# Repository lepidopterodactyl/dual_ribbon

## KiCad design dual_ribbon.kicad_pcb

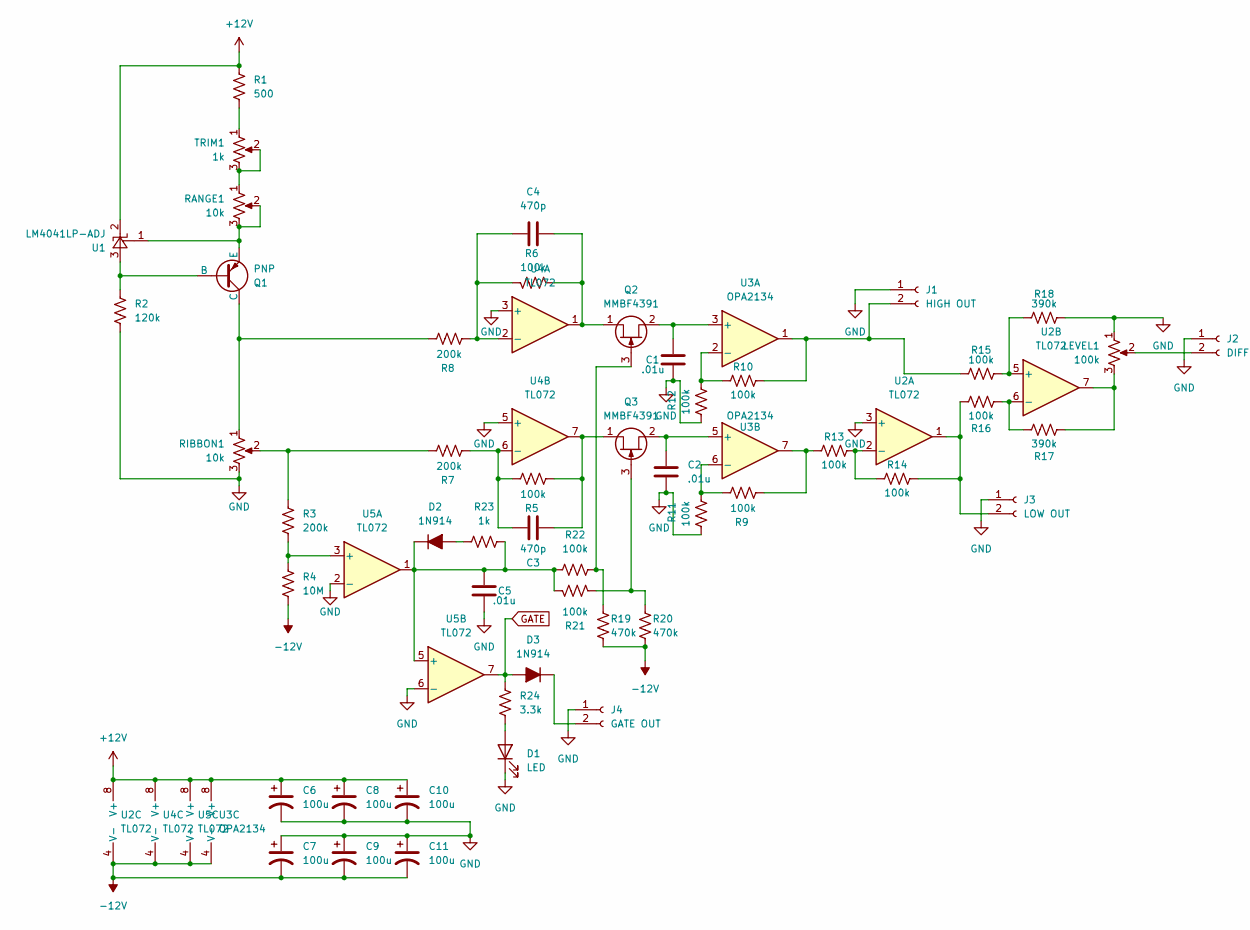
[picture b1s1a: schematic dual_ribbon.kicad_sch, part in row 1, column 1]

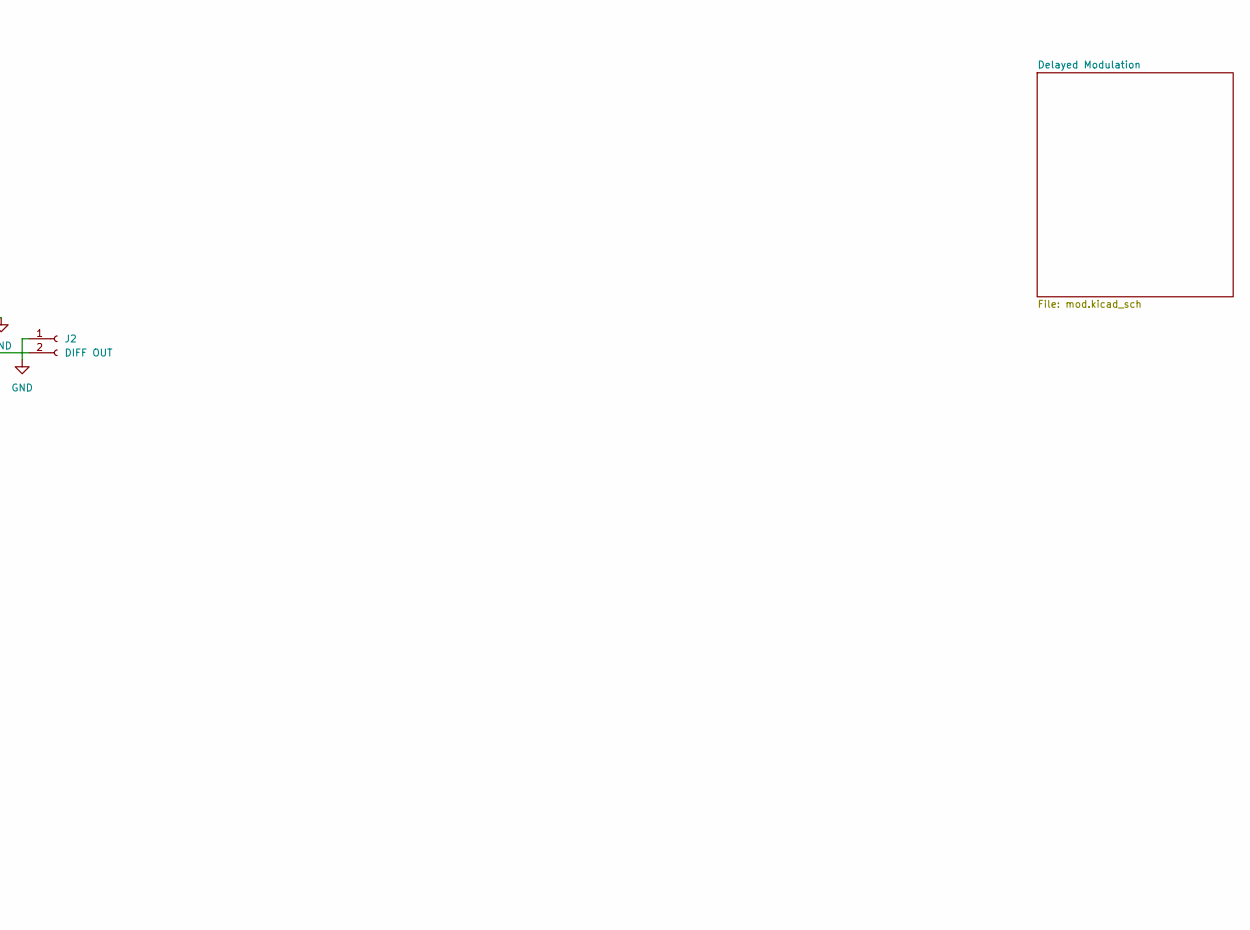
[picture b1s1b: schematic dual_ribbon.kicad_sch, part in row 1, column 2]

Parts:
C1, C2, C5: .01u; C_Rect_L7.2mm_W2.5mm_P5.00mm_FKS2_FKP2_MKS2_MKP2
C3, C4: 470p; C_Rect_L7.2mm_W2.5mm_P5.00mm_FKS2_FKP2_MKS2_MKP2
C6, C7, C8, C9, C10, C11: 100u; CP_Radial_D6.3mm_P2.50mm
D1: LED; LED_D3.0mm
D2, D3: 1N914; D_DO-35_SOD27_P7.62mm_Horizontal
J1: HIGH OUT; SolderWire-0.75sqmm_1x02_P4.8mm_D1.25mm_OD2.3mm
J2: DIFF OUT; SolderWire-0.75sqmm_1x02_P4.8mm_D1.25mm_OD2.3mm
J3: LOW OUT; SolderWire-0.75sqmm_1x02_P4.8mm_D1.25mm_OD2.3mm
J4: GATE OUT; SolderWire-0.75sqmm_1x02_P4.8mm_D1.25mm_OD2.3mm
LEVEL1: 100k; SolderWire-0.75sqmm_1x03_P4.8mm_D1.25mm_OD2.3mm
Q1: PNP; TO-92_Inline
Q2, Q3: MMBF4391; TO-92_Inline
R1: 500; R_Axial_DIN0207_L6.3mm_D2.5mm_P7.62mm_Horizontal
R2: 120k; R_Axial_DIN0207_L6.3mm_D2.5mm_P7.62mm_Horizontal
R3, R7, R8: 200k; R_Axial_DIN0207_L6.3mm_D2.5mm_P7.62mm_Horizontal
R4: 10M; R_Axial_DIN0207_L6.3mm_D2.5mm_P7.62mm_Horizontal
R5, R6, R9, R10, R11, R12, R13, R14, R15, R16, R21, R22: 100k; R_Axial_DIN0207_L6.3mm_D2.5mm_P7.62mm_Horizontal
R17, R18: 390k; R_Axial_DIN0207_L6.3mm_D2.5mm_P7.62mm_Horizontal
R19, R20: 470k; R_Axial_DIN0207_L6.3mm_D2.5mm_P7.62mm_Horizontal
R23: 1k; R_Axial_DIN0207_L6.3mm_D2.5mm_P7.62mm_Horizontal
R24: 3.3k; R_Axial_DIN0207_L6.3mm_D2.5mm_P7.62mm_Horizontal
RANGE1: 10k; SolderWire-0.75sqmm_1x03_P4.8mm_D1.25mm_OD2.3mm
RIBBON1: 10k; SolderWire-0.75sqmm_1x03_P4.8mm_D1.25mm_OD2.3mm
TRIM1: 1k; SolderWire-0.75sqmm_1x03_P4.8mm_D1.25mm_OD2.3mm
U1: LM4041LP-ADJ; TO-92_Inline
U2, U4, U5: TL072; DIP-8_W7.62mm_Socket
U3: OPA2134; DIP-8_W7.62mm_Socket

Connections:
+12V: C6.1, C8.1, C10.1, R1.1, U1.2 (K), U2.8 (V+), U3.8 (V+), U4.8 (V+), U5.8 (V+); also elsewhere on the board
-12V: C7.2, C9.2, C11.2, R4.2, R19.1, R20.1, U2.4 (V-), U3.4 (V-), U4.4 (V-), U5.4 (V-); also elsewhere on the board
GATE: D3.2 (A), R24.1, U5.7; also elsewhere on the board
GND: C1.2, C2.2, C5.2, C6.2, C7.1, C8.2, C9.1, C10.2, C11.1, D1.1 (K), J1.1, J2.1, J3.1, J4.1, LEVEL1.1, R2.2, R11.2, R12.2, R18.2, RIBBON1.3, U2.3 (+), U4.3 (+), U4.5 (+), U5.2 (-), U5.6 (-); also elsewhere on the board
unnamed: D1.2 (A), R24.2
unnamed: C5.1, D2.1 (K), R21.1, R22.1, R23.2, U5.1, U5.5 (+)
unnamed: D2.2 (A), R23.1
unnamed: D3.1 (K), J4.2
unnamed: J1.2, R10.2, R15.1, U3.1
unnamed: J2.2, LEVEL1.2
unnamed: J3.2, R14.2, R16.1, U2.1
unnamed: LEVEL1.3, R17.2, U2.7
unnamed: Q1.2 (B), R2.1, U1.3 (A)
unnamed: Q1.1 (C), R8.1, RIBBON1.1
unnamed: Q1.3 (E), RANGE1.2, RANGE1.3, U1.1 (FB)
unnamed: C4.2, Q2.1 (D), R6.2, U4.1
unnamed: Q2.3 (G), R19.2, R22.2
unnamed: C1.1, Q2.2 (S), U3.3 (+)
unnamed: C3.1, Q3.1 (D), R5.2, U4.7
unnamed: Q3.3 (G), R20.2, R21.2
unnamed: C2.1, Q3.2 (S), U3.5 (+)
unnamed: R1.2, TRIM1.1
unnamed: R3.2, R7.1, RIBBON1.2
unnamed: R9.2, R13.1, U3.7
unnamed: RANGE1.1, TRIM1.2, TRIM1.3
unnamed: R13.2, R14.1, U2.2 (-)
unnamed: R15.2, R18.1, U2.5 (+)
unnamed: R16.2, R17.1, U2.6 (-)
unnamed: R10.1, R12.1, U3.2 (-)
unnamed: R9.1, R11.1, U3.6 (-)
unnamed: C4.1, R6.1, R8.2, U4.2 (-)
unnamed: C3.2, R5.1, R7.2, U4.6 (-)
unnamed: R3.1, R4.1, U5.3 (+)

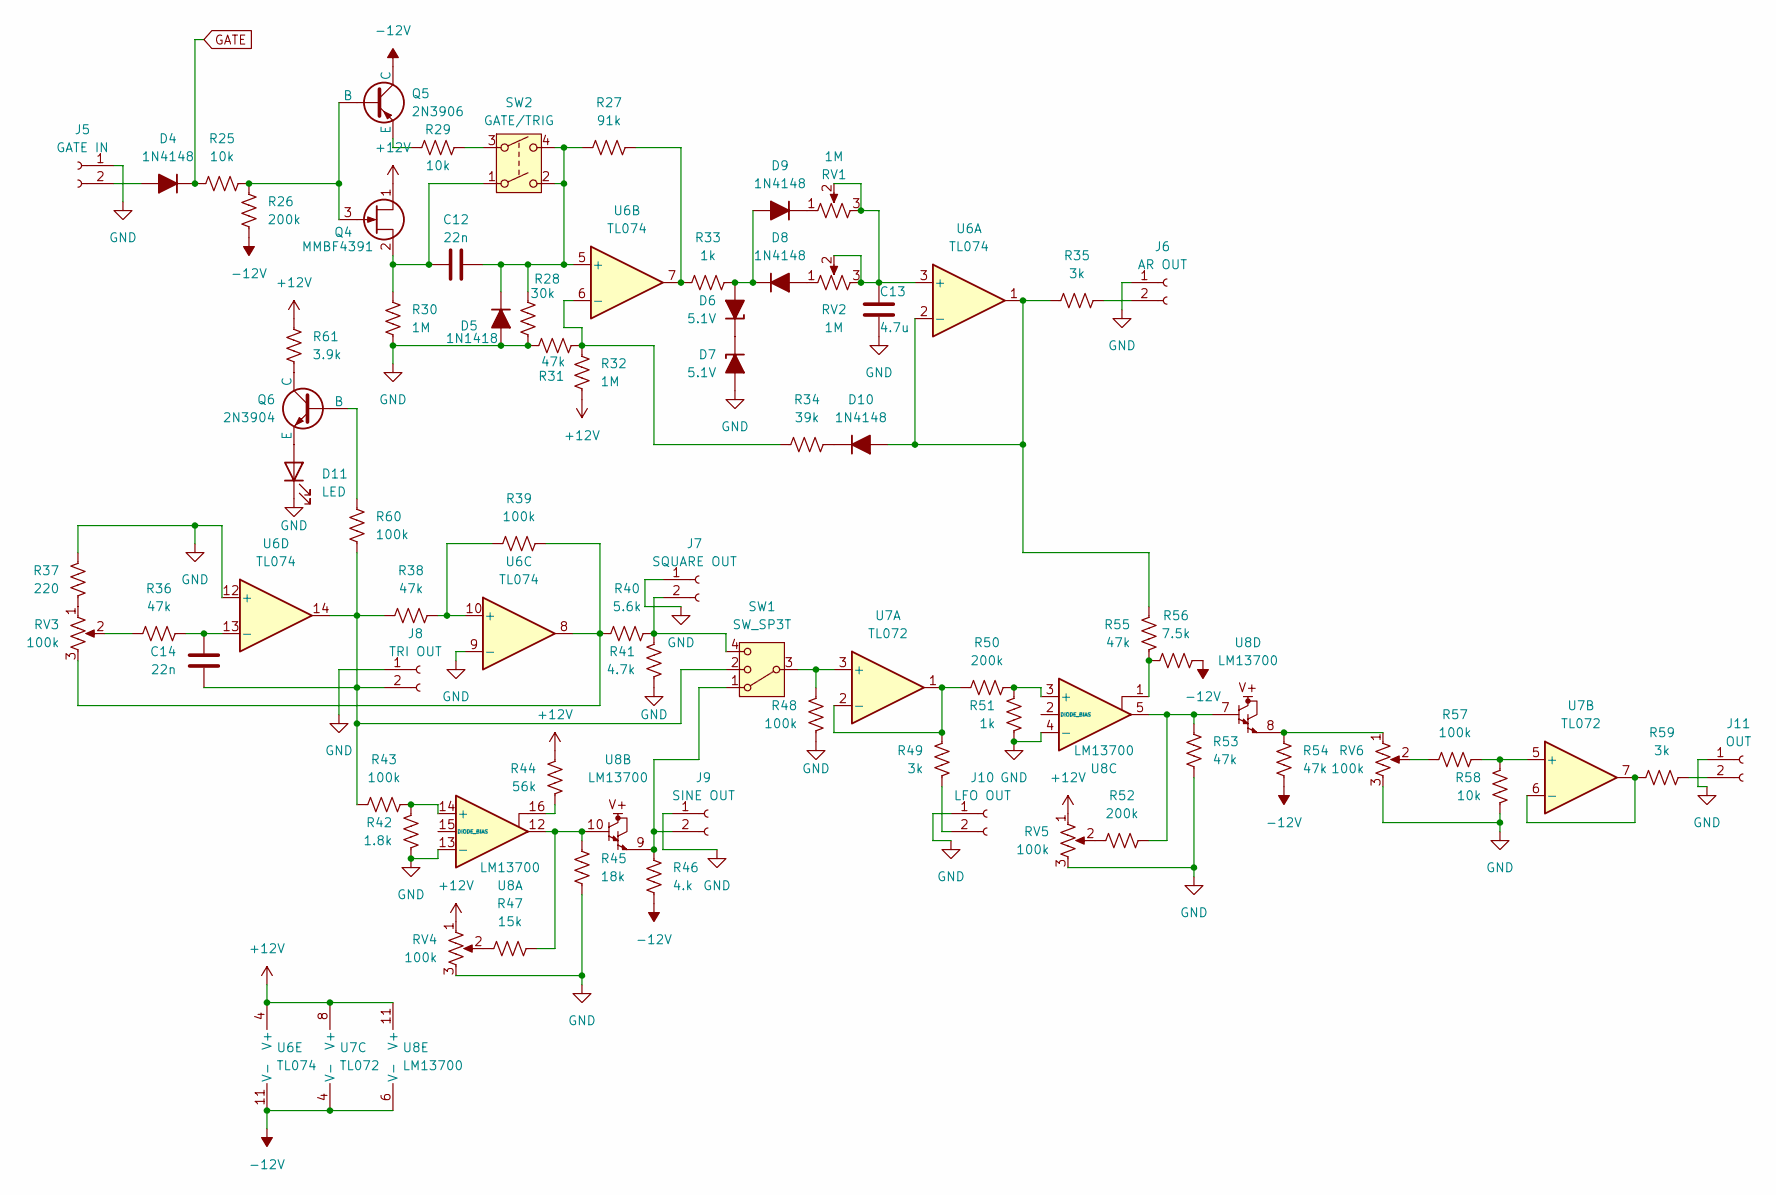
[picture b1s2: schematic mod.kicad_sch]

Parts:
C12, C14: 22n; C_Disc_D3.0mm_W2.0mm_P2.50mm
C13: 4.7u; C_Radial_D6.3mm_H5.0mm_P2.50mm
D4, D8, D9, D10: 1N4148; D_DO-35_SOD27_P7.62mm_Horizontal
D5: 1N1418; D_DO-35_SOD27_P7.62mm_Horizontal
D6, D7: 5.1V; D_DO-35_SOD27_P7.62mm_Horizontal
D11: LED; LED_D3.0mm
J5: GATE IN; SolderWire-0.75sqmm_1x02_P4.8mm_D1.25mm_OD2.3mm
J6: AR OUT; SolderWire-0.75sqmm_1x02_P4.8mm_D1.25mm_OD2.3mm
J7: SQUARE OUT; SolderWire-0.75sqmm_1x02_P4.8mm_D1.25mm_OD2.3mm
J8: TRI OUT; SolderWire-0.75sqmm_1x02_P4.8mm_D1.25mm_OD2.3mm
J9: SINE OUT; SolderWire-0.75sqmm_1x02_P4.8mm_D1.25mm_OD2.3mm
J10: LFO OUT; SolderWire-0.75sqmm_1x02_P4.8mm_D1.25mm_OD2.3mm
J11: OUT; SolderWire-0.75sqmm_1x02_P4.8mm_D1.25mm_OD2.3mm
Q4: MMBF4391; TO-92_Inline
Q5: 2N3906; TO-92_Inline
Q6: 2N3904; TO-92_Inline
R25, R29, R58: 10k; R_Axial_DIN0207_L6.3mm_D2.5mm_P7.62mm_Horizontal
R26, R50, R52: 200k; R_Axial_DIN0207_L6.3mm_D2.5mm_P7.62mm_Horizontal
R27: 91k; R_Axial_DIN0207_L6.3mm_D2.5mm_P7.62mm_Horizontal
R28: 30k; R_Axial_DIN0207_L6.3mm_D2.5mm_P7.62mm_Horizontal
R30, R32: 1M; R_Axial_DIN0207_L6.3mm_D2.5mm_P7.62mm_Horizontal
R31, R36, R38, R53, R54, R55: 47k; R_Axial_DIN0207_L6.3mm_D2.5mm_P7.62mm_Horizontal
R33, R51: 1k; R_Axial_DIN0207_L6.3mm_D2.5mm_P7.62mm_Horizontal
R34: 39k; R_Axial_DIN0207_L6.3mm_D2.5mm_P7.62mm_Horizontal
R35, R49, R59: 3k; R_Axial_DIN0207_L6.3mm_D2.5mm_P7.62mm_Horizontal
R37: 220; R_Axial_DIN0207_L6.3mm_D2.5mm_P7.62mm_Horizontal
R39, R43, R48, R57, R60: 100k; R_Axial_DIN0207_L6.3mm_D2.5mm_P7.62mm_Horizontal
R40: 5.6k; R_Axial_DIN0207_L6.3mm_D2.5mm_P7.62mm_Horizontal
R41: 4.7k; R_Axial_DIN0207_L6.3mm_D2.5mm_P7.62mm_Horizontal
R42: 1.8k; R_Axial_DIN0207_L6.3mm_D2.5mm_P7.62mm_Horizontal
R44: 56k; R_Axial_DIN0207_L6.3mm_D2.5mm_P7.62mm_Horizontal
R45: 18k; R_Axial_DIN0207_L6.3mm_D2.5mm_P7.62mm_Horizontal
R46: 4.k; R_Axial_DIN0207_L6.3mm_D2.5mm_P7.62mm_Horizontal
R47: 15k; R_Axial_DIN0207_L6.3mm_D2.5mm_P7.62mm_Horizontal
R56: 7.5k; R_Axial_DIN0207_L6.3mm_D2.5mm_P7.62mm_Horizontal
R61: 3.9k; R_Axial_DIN0207_L6.3mm_D2.5mm_P7.62mm_Horizontal
RV1, RV2: 1M; SolderWire-0.75sqmm_1x03_P4.8mm_D1.25mm_OD2.3mm
RV3, RV4, RV5, RV6: 100k; SolderWire-0.75sqmm_1x03_P4.8mm_D1.25mm_OD2.3mm
SW1: SW_SP3T; SolderWire-0.75sqmm_1x04_P4.8mm_D1.25mm_OD2.3mm
SW2: GATE/TRIG; SolderWire-0.75sqmm_1x04_P4.8mm_D1.25mm_OD2.3mm
U6: TL074; DIP-14_W7.62mm_Socket
U7: TL072; DIP-8_W7.62mm_Socket
U8: LM13700; DIP-16_W7.62mm_Socket

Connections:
+12V: Q4.1 (D), R32.2, R44.2, R61.1, RV4.1, RV5.1, U6.4 (V+), U7.8 (V+), U8.11 (V+); also elsewhere on the board
-12V: Q5.1 (C), R26.1, R46.1, R54.1, R56.2, U6.11 (V-), U7.4 (V-), U8.6 (V-); also elsewhere on the board
GATE: D4.1 (K), R25.1; also elsewhere on the board
GND: C13.2, D5.2 (A), D7.2 (A), D11.1 (K), J5.1, J6.1, J7.1, J8.1, J9.1, J10.1, J11.1, R28.1, R30.2, R31.1, R37.2, R41.1, R42.1, R45.1, R48.1, R51.1, R53.1, R58.1, RV4.3, RV5.3, RV6.3, U6.9 (-), U6.12 (+), U8.4 (-), U8.13 (-); also elsewhere on the board
unnamed: D4.2 (A), J5.2
unnamed: C12.2, D5.1 (K), R27.1, R28.2, SW2.2, SW2.4, U6.5 (+)
unnamed: D6.2 (A), D8.1 (K), D9.2 (A), R33.2
unnamed: D6.1 (K), D7.1 (K)
unnamed: D8.2 (A), RV2.1
unnamed: D9.1 (K), RV1.1
unnamed: D10.2 (A), R35.1, R55.2, U6.1, U6.2 (-)
unnamed: D10.1 (K), R34.2
unnamed: D11.2 (A), Q6.3 (E)
unnamed: J6.2, R35.2
unnamed: J7.2, R40.2, R41.2, SW1.4
unnamed: C14.2, J8.2, R38.1, R43.1, R60.2, SW1.2, U6.14
unnamed: J9.2, R46.2, SW1.1, U8.9
unnamed: J10.2, R49.1
unnamed: J11.2, R59.2
unnamed: Q4.3 (G), Q5.2 (B), R25.2, R26.2
unnamed: C12.1, Q4.2 (S), R30.1, SW2.1
unnamed: Q5.3 (E), R29.1
unnamed: Q6.2 (B), R60.1
unnamed: Q6.1 (C), R61.2
unnamed: R27.2, R33.1, U6.7
unnamed: R29.2, SW2.3
unnamed: R36.1, RV3.2
unnamed: R37.1, RV3.1
unnamed: R39.2, R40.1, RV3.3, U6.8
unnamed: R44.1, U8.16
unnamed: R45.2, R47.2, U8.10, U8.12
unnamed: R47.1, RV4.2
unnamed: R52.1, RV5.2
unnamed: R52.2, R53.2, U8.5, U8.7
unnamed: R54.2, RV6.1, U8.8
unnamed: R55.1, R56.1, U8.1
unnamed: R57.1, RV6.2
unnamed: C13.1, RV1.2, RV1.3, RV2.2, RV2.3, U6.3 (+)
unnamed: R31.2, R32.1, R34.1, U6.6 (-)
unnamed: R38.2, R39.1, U6.10 (+)
unnamed: C14.1, R36.2, U6.13 (-)
unnamed: R48.2, SW1.3, U7.3 (+)
unnamed: R49.2, R50.1, U7.1, U7.2 (-)
unnamed: R57.2, R58.2, U7.5 (+)
unnamed: R59.1, U7.6 (-), U7.7
unnamed: R42.2, R43.2, U8.14 (+)
unnamed: R50.2, R51.2, U8.3 (+)

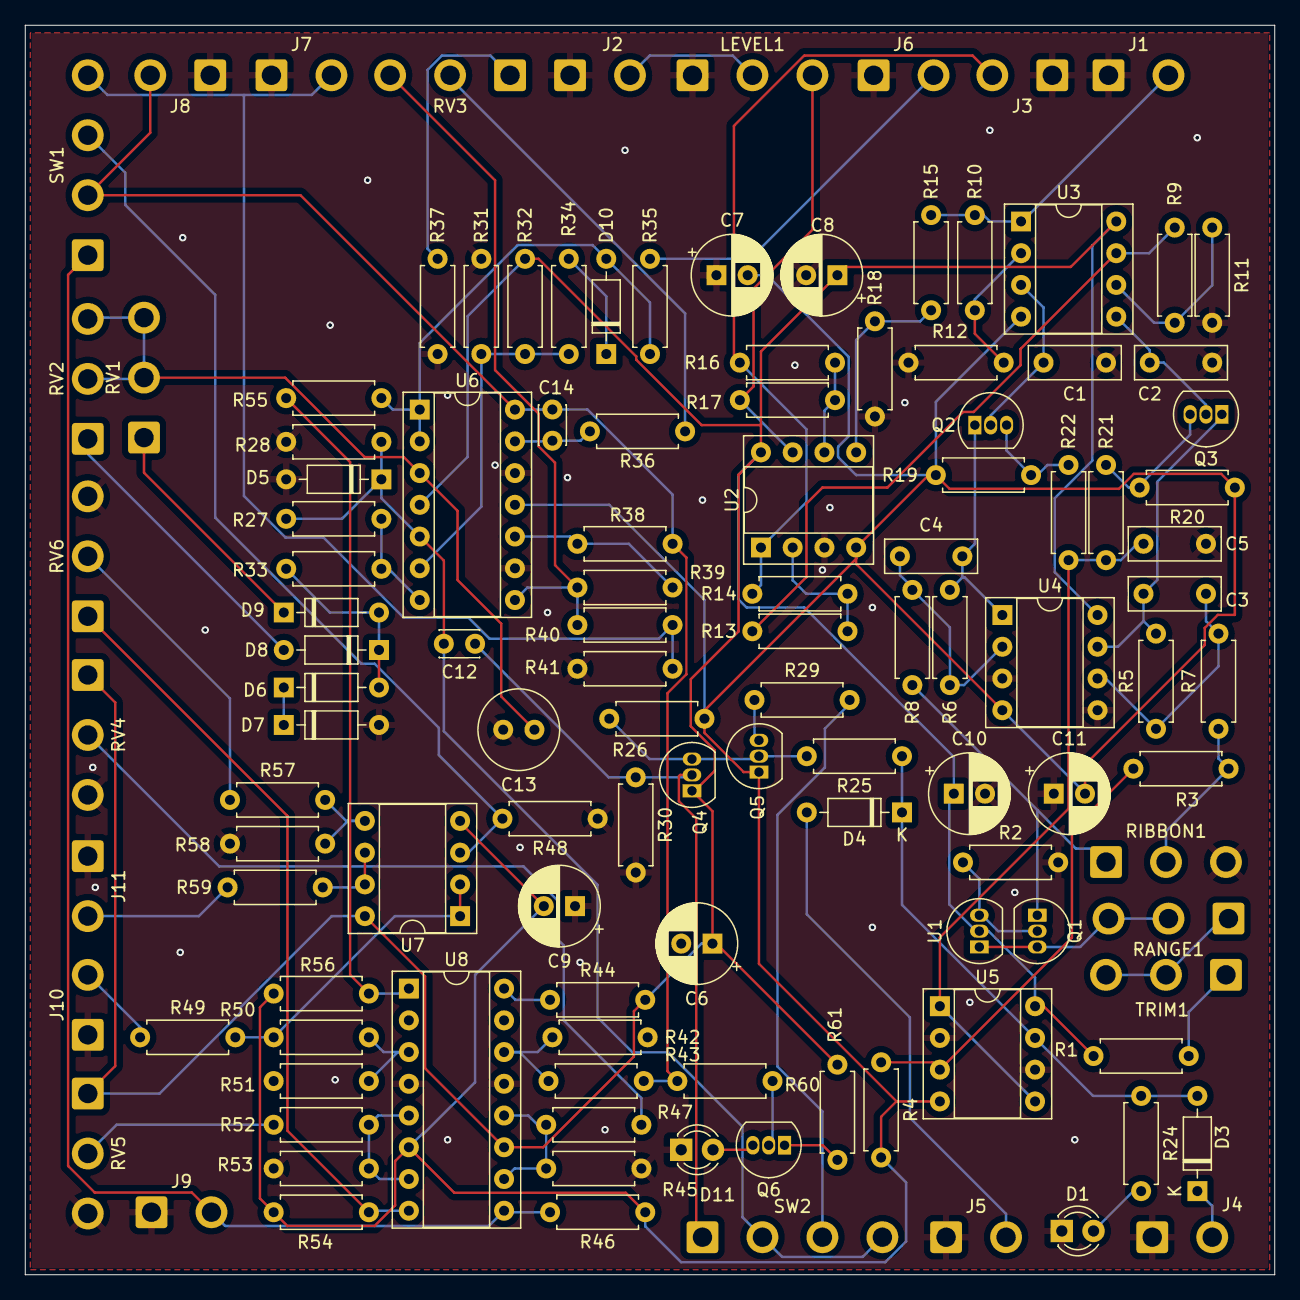
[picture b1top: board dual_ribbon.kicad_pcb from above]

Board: 2 copper layers, 100.0 x 100.0 mm, 121 parts (0 on the bottom side), 75 nets.

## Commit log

2024-06-04 Initial file push
2024-06-05 Began wiring
    Did not finish wiring
2024-06-05 Realistically this shouldn't be here
2024-06-05 Got rid of files that shouldn't be tracked
2024-06-06 Finish schematic and assign footprints
2024-06-06 Begin PCB
2024-06-10 Minor schematic fixes
2024-06-10 Layout mostly finished
2024-06-10 Ignore some files
2024-06-10 Did most of the routing
2024-06-10 Change parts to THT and do a test layout and route
2024-06-10 Redid the routing
2024-06-10 Do gerbers
2024-06-10 Add delayed modulation to use up more board space
2024-06-11 Finish schematic for modulation
2024-06-11 Schematic cleanup and placement
2024-06-13 Did the combined layout
2024-06-17 Did routing
